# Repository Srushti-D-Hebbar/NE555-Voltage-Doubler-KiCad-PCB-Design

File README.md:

# NE555 Voltage Doubler – KiCad PCB Design

This project is a compact 2-layer voltage doubler PCB designed in KiCad 10 around an NE555D timer-based circuit. The project was developed to gain hands-on experience with the complete PCB design workflow, from creating the circuit schematic and selecting component footprints to designing the physical board layout, routing the PCB, and reviewing the final design in 3D.

The circuit consists of an NE555D timer, resistors, capacitors, and diodes arranged to implement the voltage-doubling stage. The design also includes dedicated 2-pin input and output connectors. Through-hole components were used throughout the board, with the component placement arranged to keep the PCB compact and the connections clearly organized.

The PCB was designed as a 2-layer board, using both copper layers for routing and incorporating copper-filled areas into the layout. Particular attention was given to component positioning, trace routing, silkscreen references, connector placement, and overall board organization. The final PCB was then visualized using KiCad's 3D Viewer to inspect the physical appearance and component arrangement of the design.

The project provided practical experience in taking a circuit from a schematic representation to a complete PCB layout. It strengthened my understanding of schematic capture, footprint selection, through-hole PCB design, component placement, multi-layer routing, copper zones, silkscreen organization, and KiCad's 3D visualization workflow.

Overall, this project served as a practical exercise in PCB design and helped bridge the gap between circuit-level design and physical hardware implementation.

---
## Overview

This project is a PCB implementation of an NE555-based voltage doubler circuit.

The circuit uses an NE555D timer, resistors, capacitors, and diodes to implement the voltage-doubling circuit, with dedicated input and output connectors.

The PCB was designed as a hands-on exercise in taking a circuit from **schematic → PCB layout → routing → 3D visualization** using KiCad 10.

---
## Features

- NE555D-based voltage doubler circuit
- 2-layer PCB design
- Compact component placement
- Through-hole components
- Dedicated input and output connectors
- Front and back copper routing
- Copper-filled PCB areas
- Clearly labeled component references
- Organized silkscreen
- 3D PCB visualization
- Editable KiCad design files

---
## Software Used

- **KiCad 10**
  - Schematic Editor
  - PCB Editor
  - 3D Viewer

---
## PCB Design

The PCB was designed as a compact 2-layer board, with through-hole components arranged for a clean and organized layout.

### Front View

### Back View

---
## PCB Layout

The PCB layout includes component placement, routing across both copper layers, copper-filled areas, and organized silkscreen markings.

### Front Copper / Layout

### Back Copper / Layout

---
## Schematic

The schematic contains the NE555 timer section, timing components, diode-capacitor voltage doubler section, power connections, and input/output connectors.

---
## Learning Outcomes

This project helped strengthen my practical understanding of the **PCB design workflow using KiCad**, including:

- Schematic capture
- Component and footprint selection
- PCB component placement
- Through-hole PCB design
- 2-layer PCB routing
- Copper zone and fill handling
- Silkscreen organization
- PCB layout visualization
- Connecting schematic design with PCB implementation
- Managing KiCad schematic, PCB, and project files

The project provided hands-on experience in translating a circuit schematic into a physically organized PCB layout.

---
## Future Improvements

Possible improvements for future iterations include:

- Further optimization of component placement and routing
- Improving PCB compactness and layout organization
- Adding additional design considerations for practical fabrication
- Exploring alternative footprints and component packages
- Fabricating the PCB and performing hardware-level testing
- Comparing the practical output with the expected circuit behavior

---
## Author

**Srushti D**
[GitHub](https://github.com/Srushti-D-Hebbar)

---
## License

This project is licensed under the MIT License — see the [LICENSE](LICENSE) file for details.

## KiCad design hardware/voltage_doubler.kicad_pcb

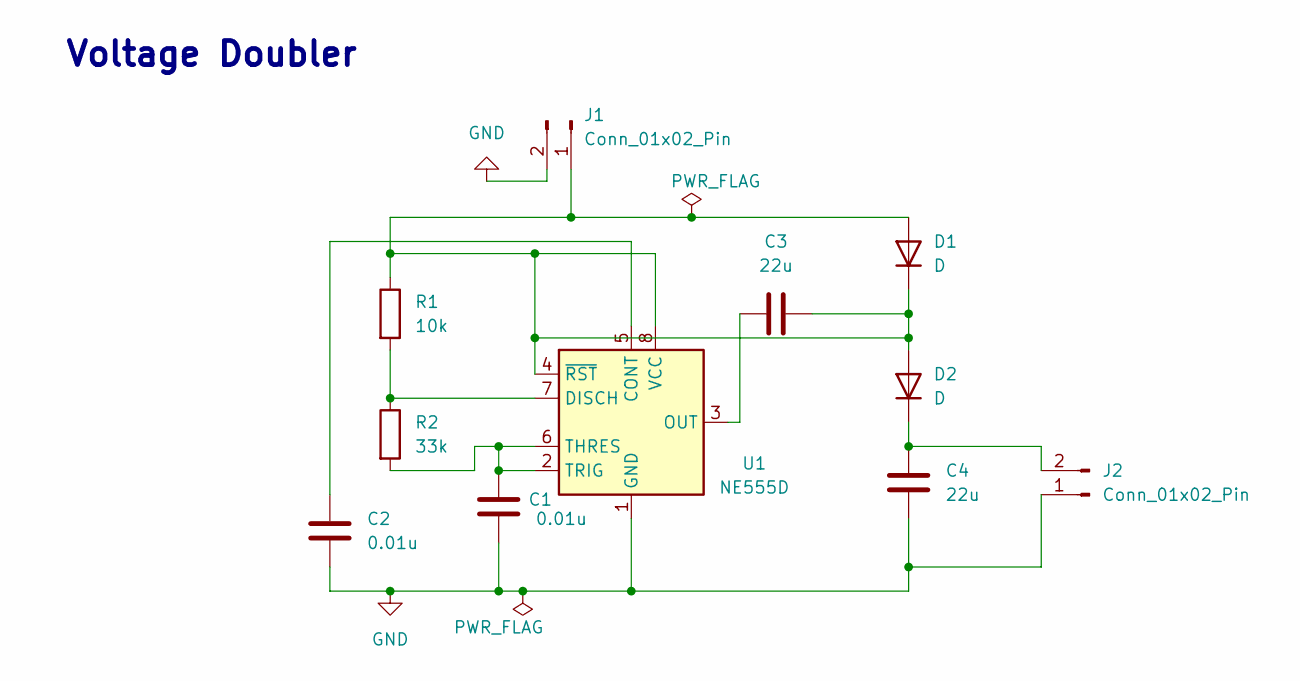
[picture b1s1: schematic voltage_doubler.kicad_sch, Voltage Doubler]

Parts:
C1, C2: 0.01u; C_Disc_D3.0mm_W1.6mm_P2.50mm
C3, C4: 22u; CP_Radial_D4.0mm_P1.50mm
D1, D2: D; D_5W_P10.16mm_Horizontal
J1, J2: Conn_01x02_Pin; PinHeader_1x02_P1.00mm_Horizontal
R1: 10k; R_Axial_DIN0204_L3.6mm_D1.6mm_P5.08mm_Horizontal
R2: 33k; R_Axial_DIN0204_L3.6mm_D1.6mm_P5.08mm_Horizontal
U1: NE555D; SOIC-8_3.9x4.9mm_P1.27mm

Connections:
GND: C1.2, C2.2, C4.2, J1.2, J2.1, U1.1 (GND)
unnamed: C3.2, D1.1 (K), D1.2 (A), D2.2 (A), J1.1, R1.1, U1.4 (~RST), U1.8 (VCC)
unnamed: C4.1, D2.1 (K), J2.2
unnamed: C2.1, U1.5 (CONT)
unnamed: R1.2, R2.1, U1.7 (DISCH)
unnamed: C3.1, U1.3 (OUT)
unnamed: C1.1, R2.2, U1.2 (TRIG), U1.6 (THRES)

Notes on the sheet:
Voltage Doubler

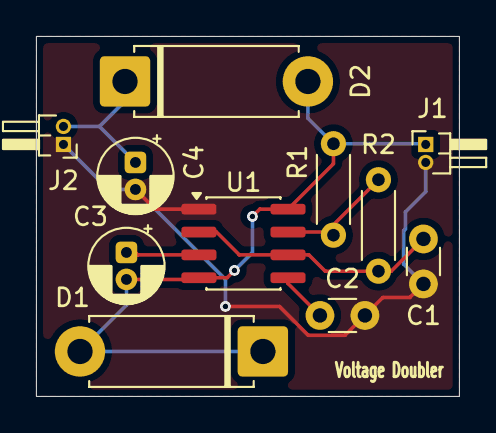
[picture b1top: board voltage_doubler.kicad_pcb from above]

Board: 2 copper layers, 23.5 x 20.0 mm, 11 parts (0 on the bottom side), 7 nets.
